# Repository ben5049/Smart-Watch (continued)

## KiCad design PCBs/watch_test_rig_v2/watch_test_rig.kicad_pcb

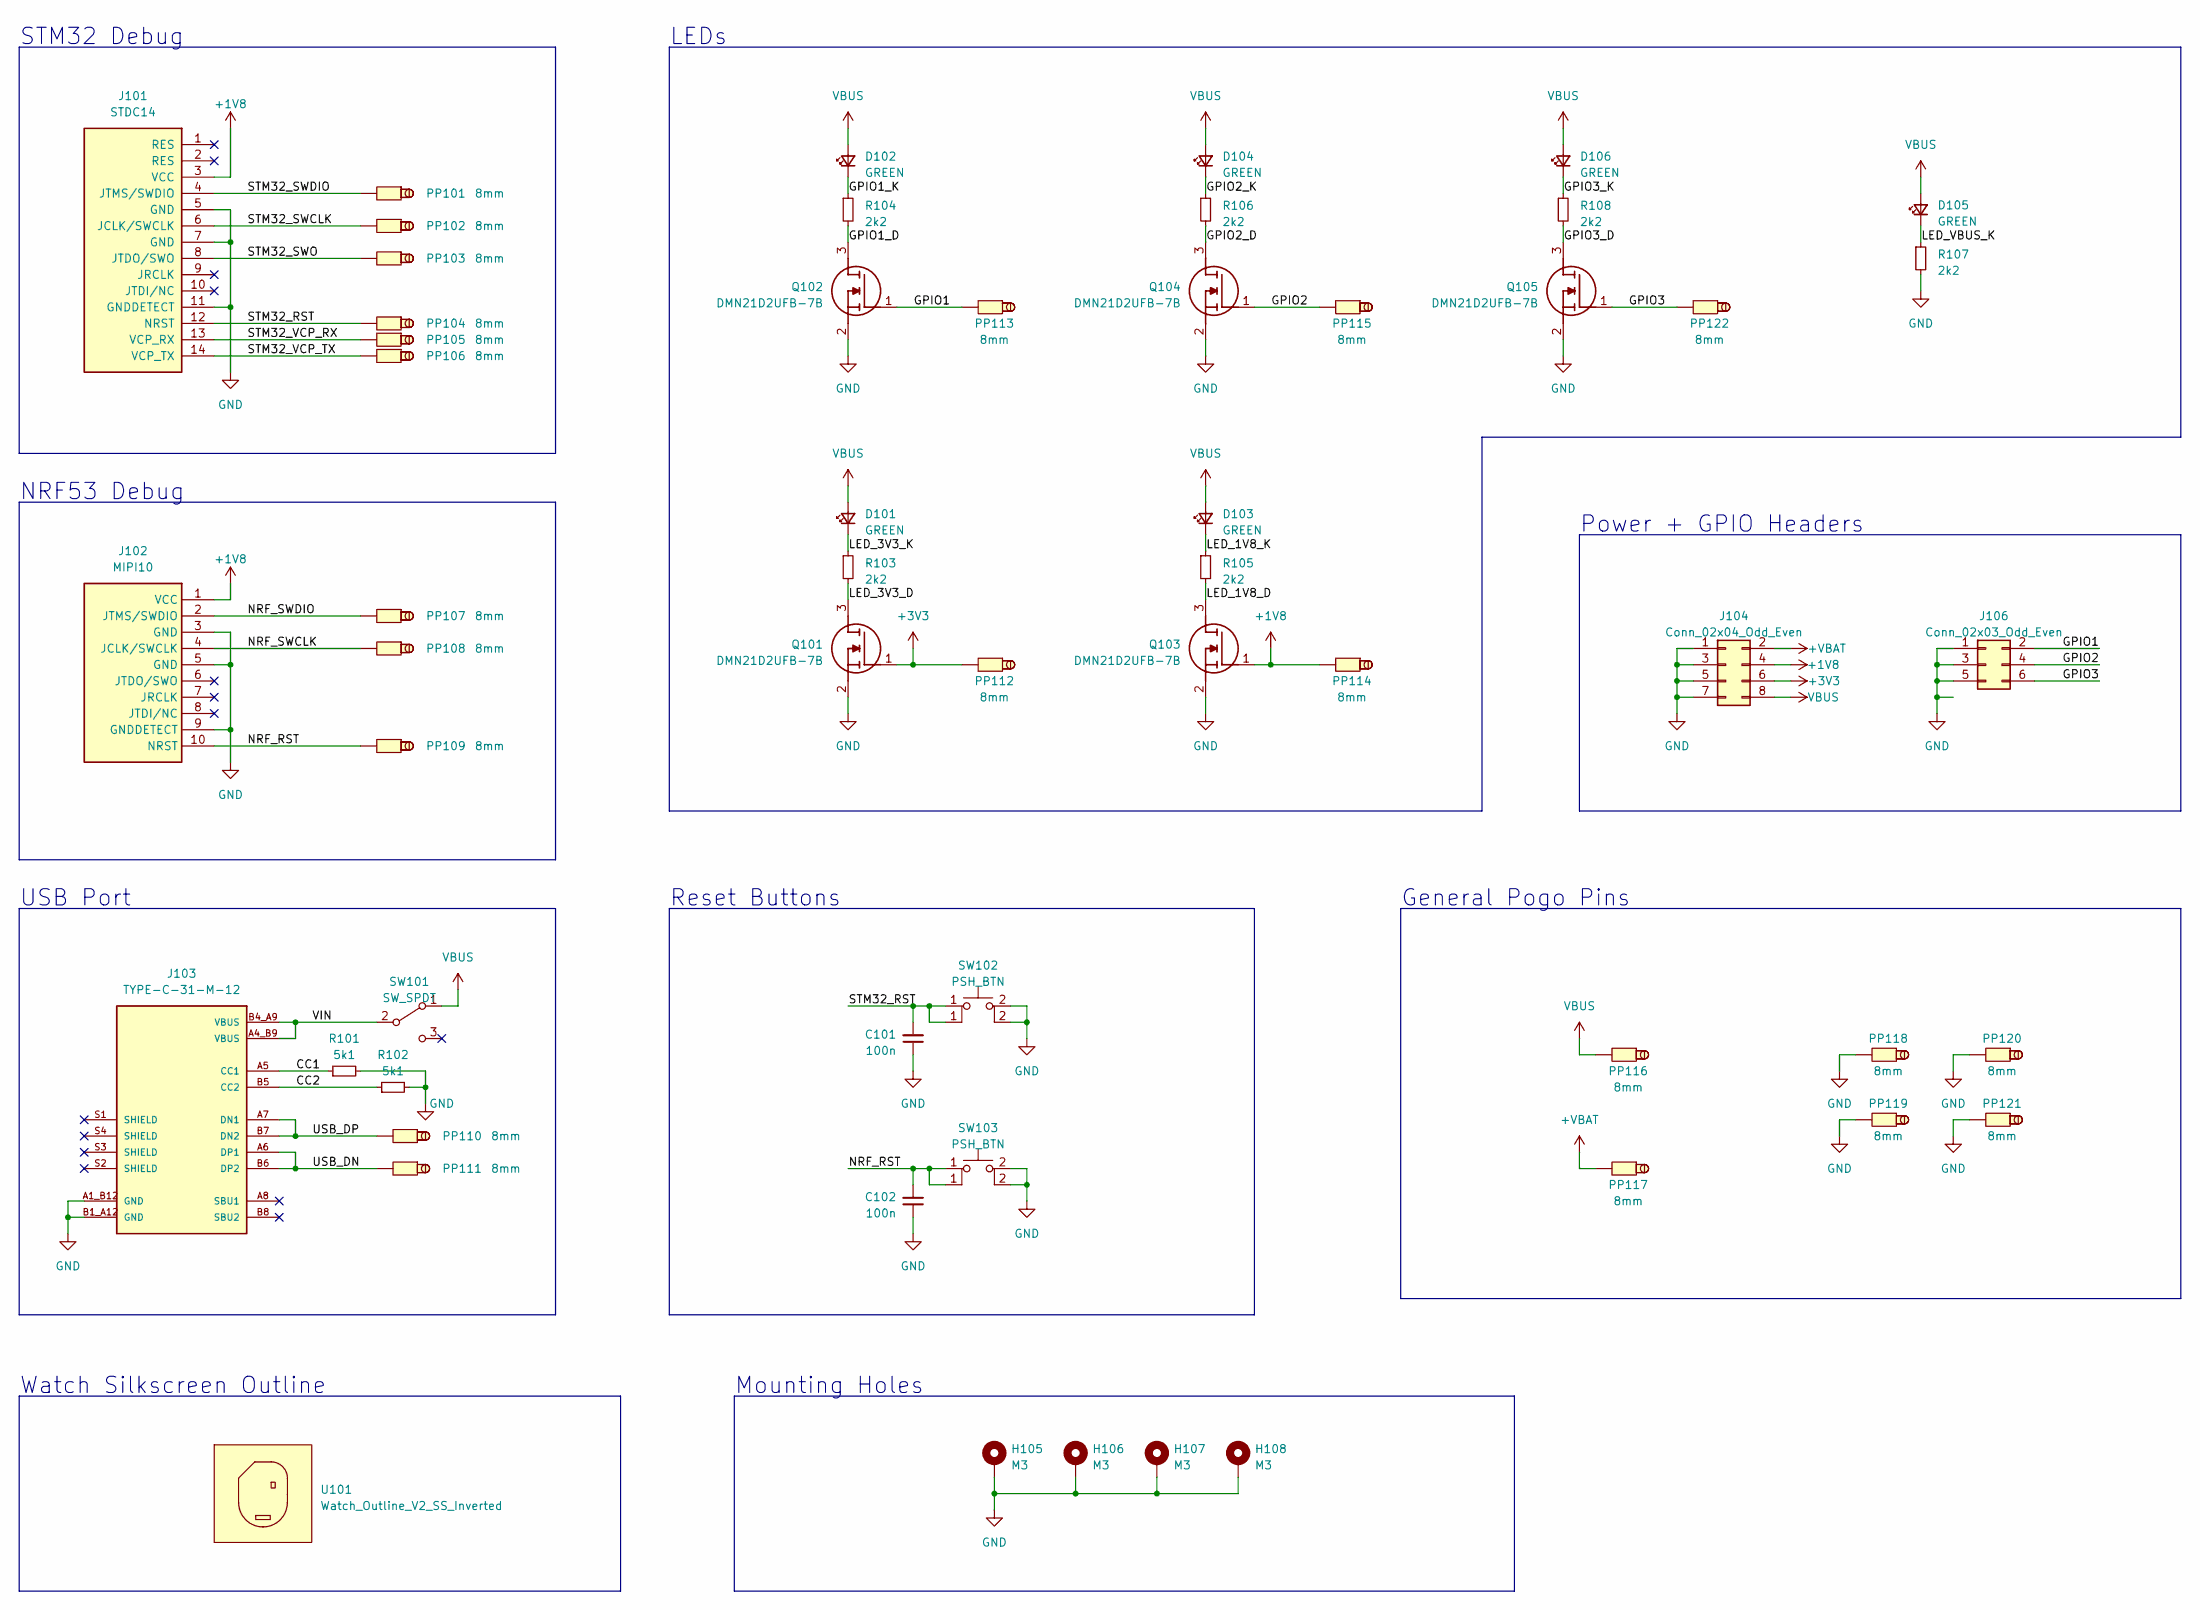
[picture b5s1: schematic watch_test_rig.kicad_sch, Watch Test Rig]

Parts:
C101, C102: 100n; C_0402_1005Metric
D101, D102, D103, D104, D105, D106: GREEN; D_0603_1608Metric
H105, H106, H107, H108: M3; MountingHole_3.2mm_M3_DIN965_Pad_TopBottom
J101: STDC14
J102: MIPI10
J103: TYPE-C-31-M-12; PARTREV 2020.12.08
J104: Conn_02x04_Odd_Even; PinHeader_2x04_P2.54mm_Vertical
J106: Conn_02x03_Odd_Even; PinHeader_2x03_P2.54mm_Vertical
PP101, PP102, PP103, PP104, PP105, PP106, PP107, PP108, PP109, PP110, PP111, PP112, PP113, PP114, PP115, PP116, PP117, PP118, PP119, PP120, PP121, PP122: 8mm; Pogo_Pin_8mm_SMD
Q101, Q102, Q103, Q104, Q105: DMN21D2UFB-7B; DMN21D2UFB7B; Mouser Part Number 621-DMN21D2UFB-7B
R101, R102: 5k1; R_0402_1005Metric
R103, R104, R105, R106, R107, R108: 2k2; R_0402_1005Metric
SW101: SW_SPDT; PinHeader_1x03_P2.54mm_Vertical
SW102, SW103: PSH_BTN; SW_PUSH_6mm_H5mm
U101: Watch_Outline_V2_SS_Inverted; Watch Outline V2 SS Inverted

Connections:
+1V8: J101.3 (VCC), J102.1 (VCC), J104.4, PP114.1, Q103.1 (G)
+3V3: J104.6, PP112.1, Q101.1 (G)
+VBAT: J104.2, PP117.1
/CC1: J103.A5 (CC1), R101.1
/CC2: J103.B5 (CC2), R102.1
/GPIO1: J106.2, PP113.1, Q102.1 (G)
/GPIO1_D: Q102.3 (D), R104.2
/GPIO1_K: D102.1 (K), R104.1
/GPIO2: J106.4, PP115.1, Q104.1 (G)
/GPIO2_D: Q104.3 (D), R106.2
/GPIO2_K: D104.1 (K), R106.1
/GPIO3: J106.6, PP122.1, Q105.1 (G)
/GPIO3_D: Q105.3 (D), R108.2
/GPIO3_K: D106.1 (K), R108.1
/LED_1V8_D: Q103.3 (D), R105.2
/LED_1V8_K: D103.1 (K), R105.1
/LED_3V3_D: Q101.3 (D), R103.2
/LED_3V3_K: D101.1 (K), R103.1
/LED_VBUS_K: D105.1 (K), R107.1
/NRF_RST: C102.2, J102.10 (NRST), PP109.1, SW103.1
/NRF_SWCLK: J102.4 (JCLK/SWCLK), PP108.1
/NRF_SWDIO: J102.2 (JTMS/SWDIO), PP107.1
/STM32_RST: C101.2, J101.12 (NRST), PP104.1, SW102.1
/STM32_SWCLK: J101.6 (JCLK/SWCLK), PP102.1
/STM32_SWDIO: J101.4 (JTMS/SWDIO), PP101.1
/STM32_SWO: J101.8 (JTDO/SWO), PP103.1
/STM32_VCP_RX: J101.13 (VCP_RX), PP105.1
/STM32_VCP_TX: J101.14 (VCP_TX), PP106.1
/USB_DN: J103.A6 (DP1), J103.B6 (DP2), PP111.1
/USB_DP: J103.A7 (DN1), J103.B7 (DN2), PP110.1
/VIN: J103.A4_B9 (VBUS), J103.B4_A9 (VBUS), SW101.2 (B)
GND: C101.1, C102.1, H105.1, H106.1, H107.1, H108.1, J101.5 (GND), J101.7 (GND), J101.11 (GNDDETECT), J102.3 (GND), J102.5 (GND), J102.9 (GNDDETECT), J103.A1_B12 (GND), J103.B1_A12 (GND), J104.1, J104.3, J104.5, J104.7, J106.1, J106.3, J106.5, PP118.1, PP119.1, PP120.1, PP121.1, Q101.2 (S), Q102.2 (S), Q103.2 (S), Q104.2 (S), Q105.2 (S), R101.2, R102.2, R107.2, SW102.2, SW103.2
VBUS: D101.2 (A), D102.2 (A), D103.2 (A), D104.2 (A), D105.2 (A), D106.2 (A), J104.8, PP116.1, SW101.1 (A)

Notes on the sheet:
Mounting Holes
Watch Silkscreen Outline
STM32 Debug
USB Port
Reset Buttons
General Pogo Pins
Power + GPIO Headers
LEDs
NRF53 Debug

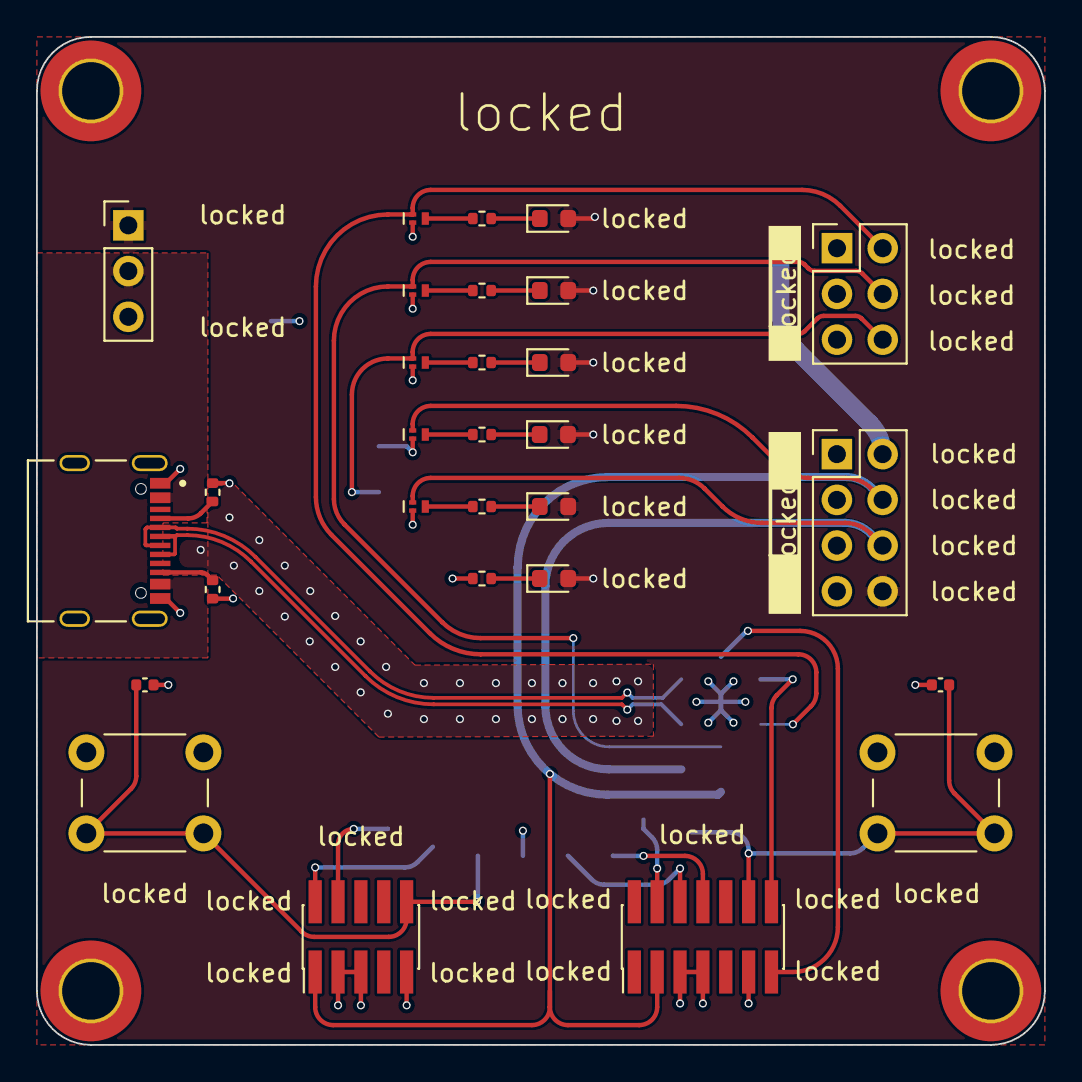
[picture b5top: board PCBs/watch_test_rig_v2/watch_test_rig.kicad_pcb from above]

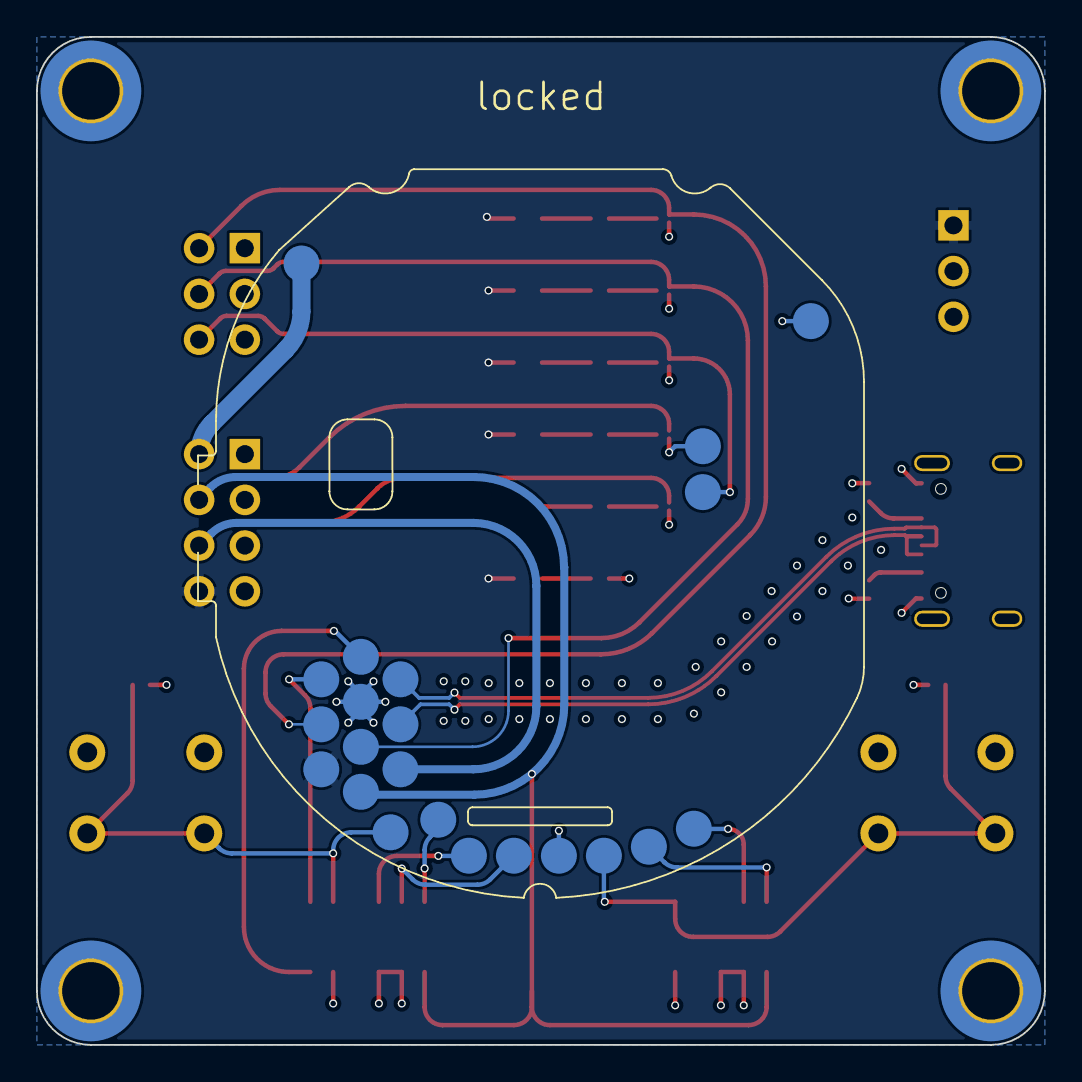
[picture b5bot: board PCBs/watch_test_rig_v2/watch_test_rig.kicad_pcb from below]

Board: 4 copper layers, 56.0 x 56.0 mm, 56 parts (22 on the bottom side), 33 nets.

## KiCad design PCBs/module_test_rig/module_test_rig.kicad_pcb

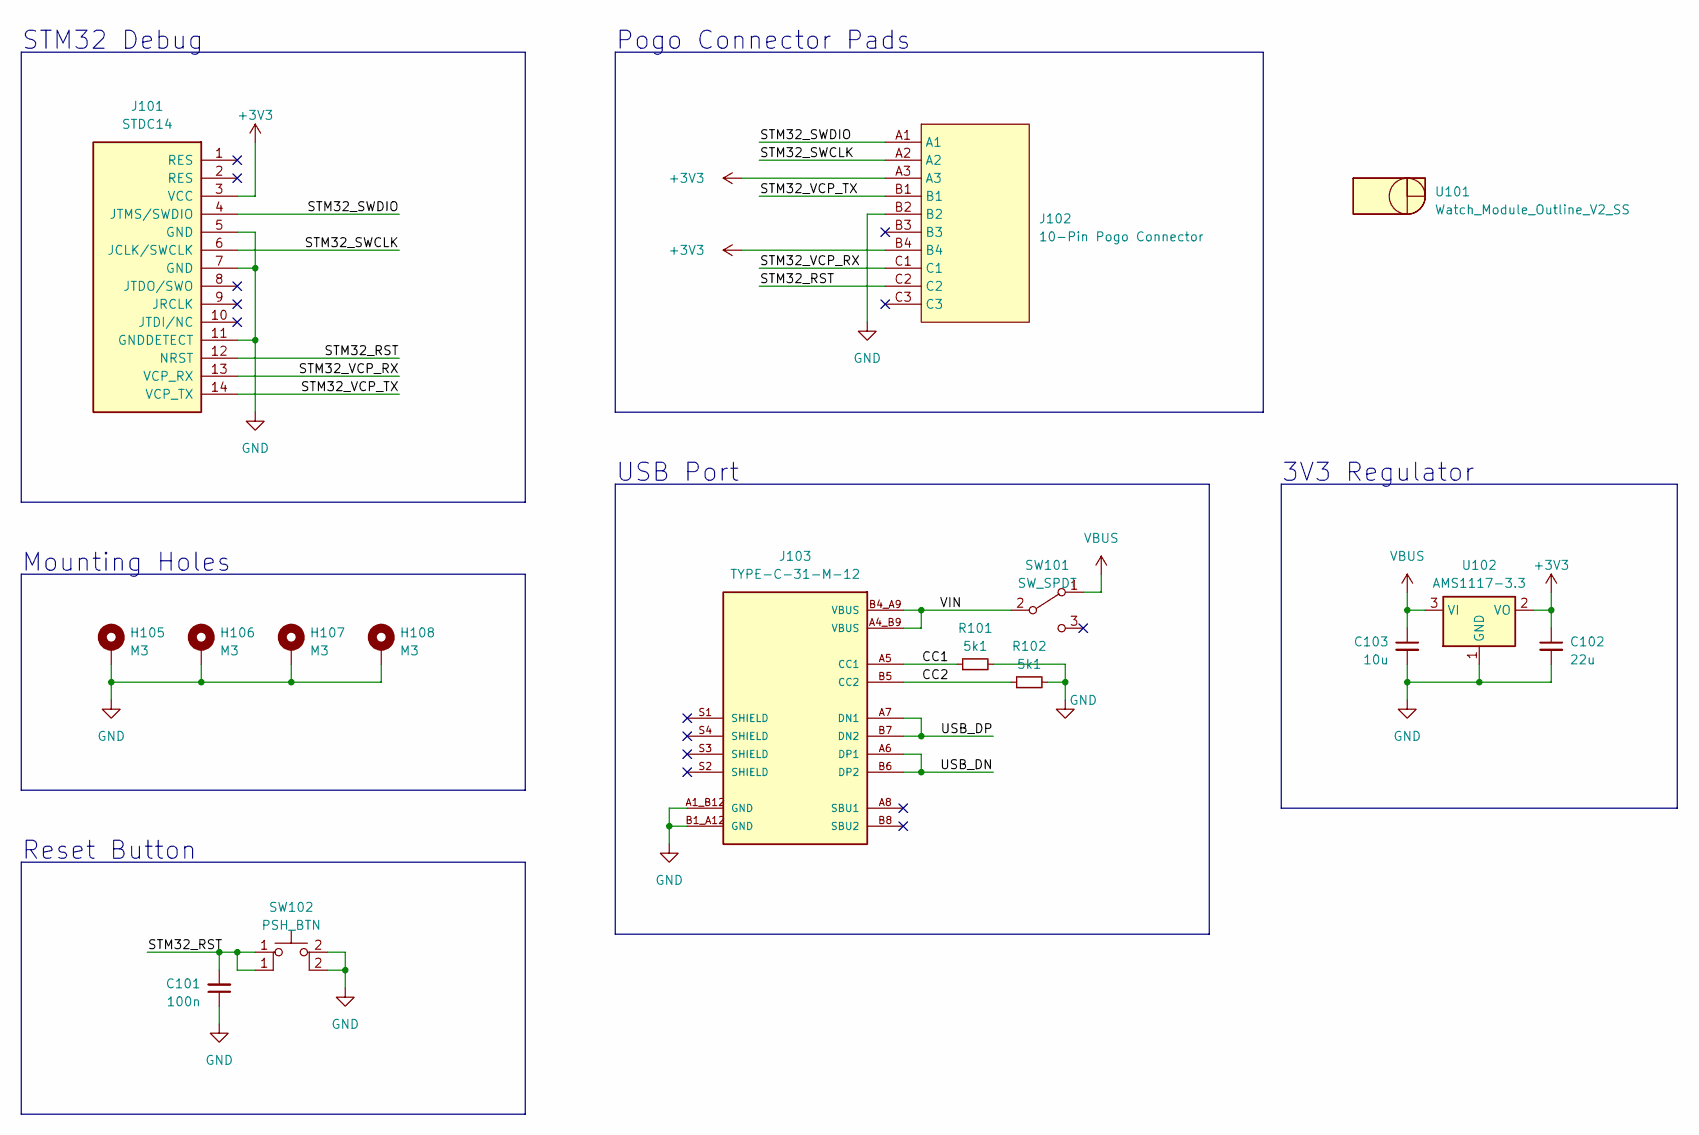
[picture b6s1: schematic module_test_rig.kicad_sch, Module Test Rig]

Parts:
C101: 100n; C_0402_1005Metric
C102: 22u; C_0402_1005Metric
C103: 10u; C_0402_1005Metric
H105, H106, H107, H108: M3; MountingHole_3.2mm_M3_DIN965_Pad_TopBottom
J101: STDC14
J102: 10-Pin Pogo Connector
J103: TYPE-C-31-M-12; PARTREV 2020.12.08
R101, R102: 5k1; R_0402_1005Metric
SW101: SW_SPDT; PinHeader_1x03_P2.54mm_Vertical
SW102: PSH_BTN; SW_PUSH_6mm_H5mm
U101: Watch_Module_Outline_V2_SS; Watch Module Outline V2 SS
U102: AMS1117-3.3; SOT-223-3_TabPin2

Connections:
+3V3: C102.1, J101.3 (VCC), J102.A3, J102.B4, U102.2 (VO)
/CC1: J103.A5 (CC1), R101.1
/CC2: J103.B5 (CC2), R102.1
/STM32_RST: C101.2, J101.12 (NRST), J102.C2, SW102.1
/STM32_SWCLK: J101.6 (JCLK/SWCLK), J102.A2
/STM32_SWDIO: J101.4 (JTMS/SWDIO), J102.A1
/STM32_VCP_RX: J101.13 (VCP_RX), J102.C1
/STM32_VCP_TX: J101.14 (VCP_TX), J102.B1
/USB_DN: J103.A6 (DP1), J103.B6 (DP2)
/USB_DP: J103.A7 (DN1), J103.B7 (DN2)
/VIN: J103.A4_B9 (VBUS), J103.B4_A9 (VBUS), SW101.2 (B)
GND: C101.1, C102.2, C103.2, H105.1, H106.1, H107.1, H108.1, J101.5 (GND), J101.7 (GND), J101.11 (GNDDETECT), J102.B2, J103.A1_B12 (GND), J103.B1_A12 (GND), R101.2, R102.2, SW102.2, U102.1 (GND)
VBUS: C103.1, SW101.1 (A), U102.3 (VI)

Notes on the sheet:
Mounting Holes
STM32 Debug
USB Port
Reset Button
Pogo Connector Pads
3V3 Regulator

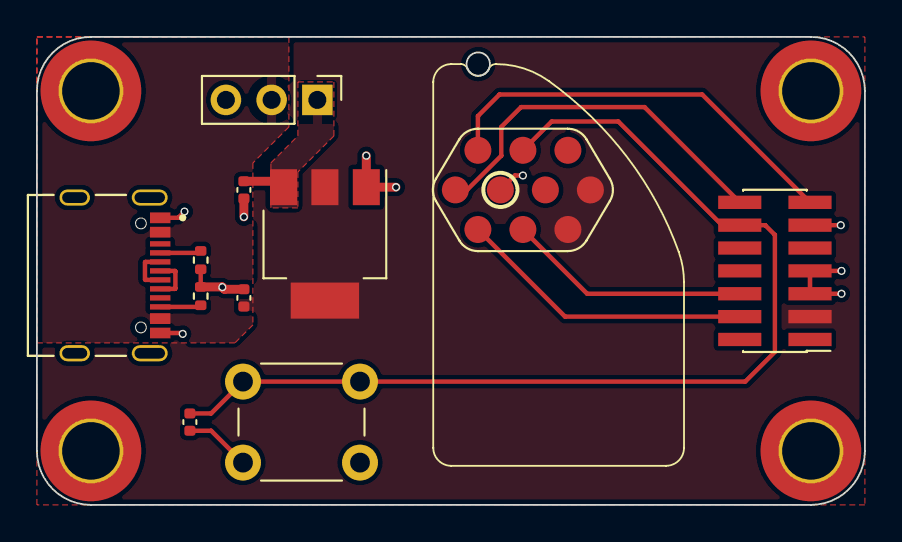
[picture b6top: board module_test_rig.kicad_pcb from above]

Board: 2 copper layers, 46.0 x 26.0 mm, 16 parts (0 on the bottom side), 13 nets.

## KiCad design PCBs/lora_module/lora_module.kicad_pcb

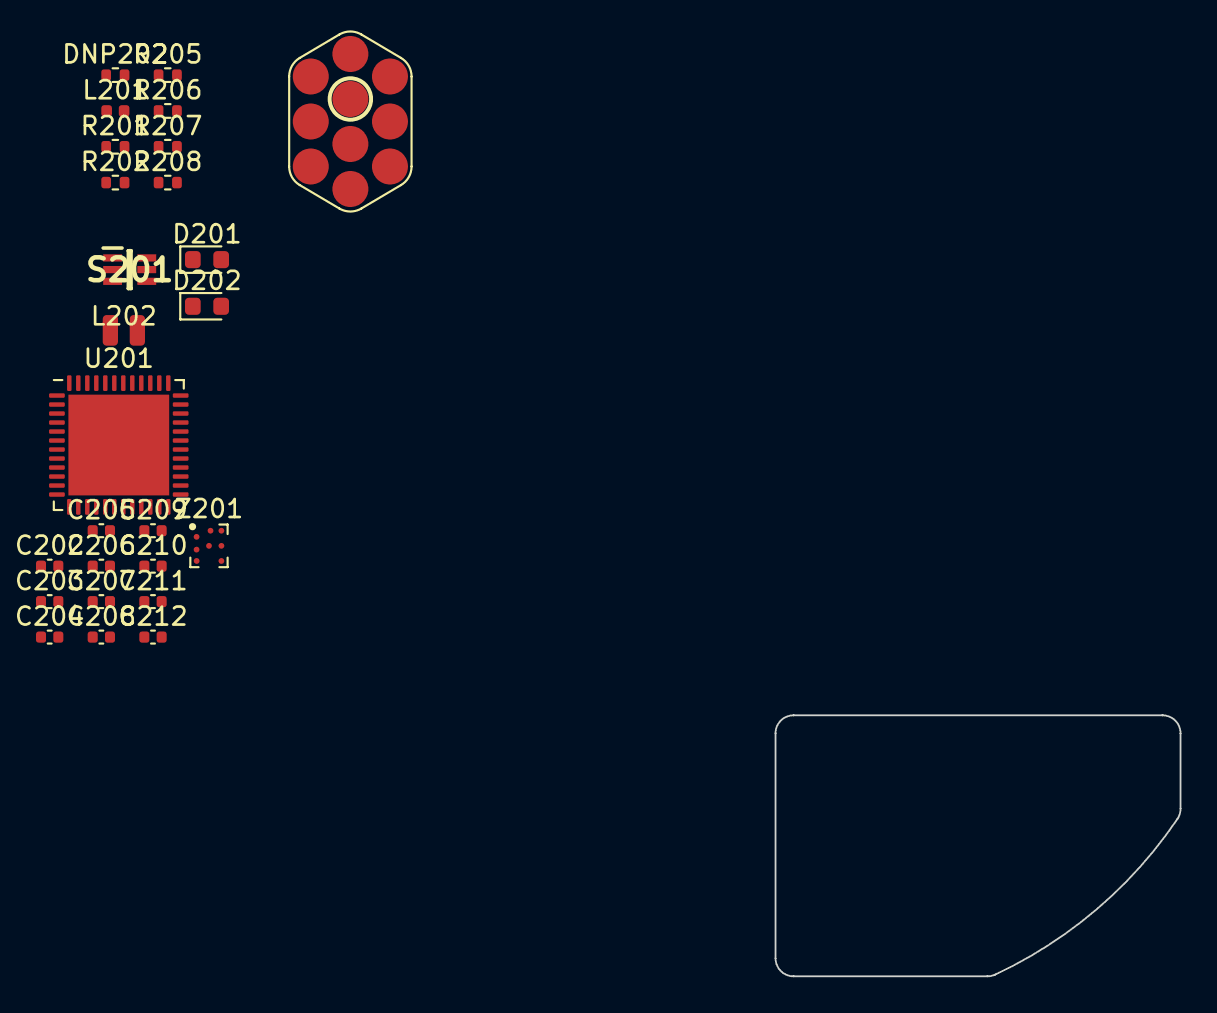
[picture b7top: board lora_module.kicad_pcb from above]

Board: 2 copper layers, 22.5 x 14.5 mm, 27 parts (0 on the bottom side), 13 nets, no tracks yet.

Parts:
C202, C203, C206, C210: 100n; C_0402_1005Metric
C204: 68p; C_0402_1005Metric
C205: 470n; C_0402_1005Metric
C207, C212: 4u7; C_0402_1005Metric
C208: 10n; C_0402_1005Metric
C209, C211: 1u; C_0402_1005Metric
D201: LEDR; LED_0603_1608Metric
D202: LEDB; LED_0603_1608Metric
DNP202: 10k; R_0402_1005Metric
J401: 10-Pin_Pogo_Connector_Male; 10-Pin Pogo Connector Male
L201: 47n; L_0402_1005Metric
L202: 15u; Inductor 0806 (2016)
R201, R202: 1k; R_0402_1005Metric
R205, R207, R208: 10k; R_0402_1005Metric
R206: 0R; R_0402_1005Metric
S201: PE42421SCAA-Z; SOT65P210X110-6N
U101: Watch_Module_Outline_V1; Watch Module Outline V1
U201: STM32WL55CCUx; QFN-48-1EP_7x7mm_P0.5mm_EP5.6x5.6mm
Z201: BALFHB-WL-02D3

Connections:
+3V3: C203.1, C206.1, C207.1, C208.1, C209.1, C210.1, C211.1, C212.1, DNP202.1, J401.A3, R207.2, R208.2
/STM32WL55/CTRL1: R208.1, S201.6 (VDD)
/STM32WL55/CTRL2: R207.1, S201.4 (CTRL)
/STM32WL55/LoRa_BOOT: DNP202.2, R205.1
/STM32WL55/LoRa_LEDB_C: D202.1 (K), R202.1
/STM32WL55/LoRa_LEDR_C: D201.1 (K), R201.1
/STM32WL55/RFI: S201.3 (RF2), Z201.C3 (RFI_IN)
/STM32WL55/RFO: S201.1 (RF1), Z201.C1 (RFO_OUT)
/STM32WL55/RFO_HP1: L201.2, R206.1
/STM32WL55/RFO_HP2: R206.2, Z201.A1 (RFO_IN)
/STM32WL55/VDDRF1V5: C205.1, L202.1
/STM32WL55/VR_PA: C202.1, C204.1, L201.1
GND: C202.2, C203.2, C204.2, C205.2, C206.2, C207.2, C208.2, C209.2, C210.2, C211.2, C212.2, J401.B2, R201.2, R202.2, R205.2, S201.2 (GND), Z201.B1 (GND), Z201.B2 (GND), Z201.C2 (GND)

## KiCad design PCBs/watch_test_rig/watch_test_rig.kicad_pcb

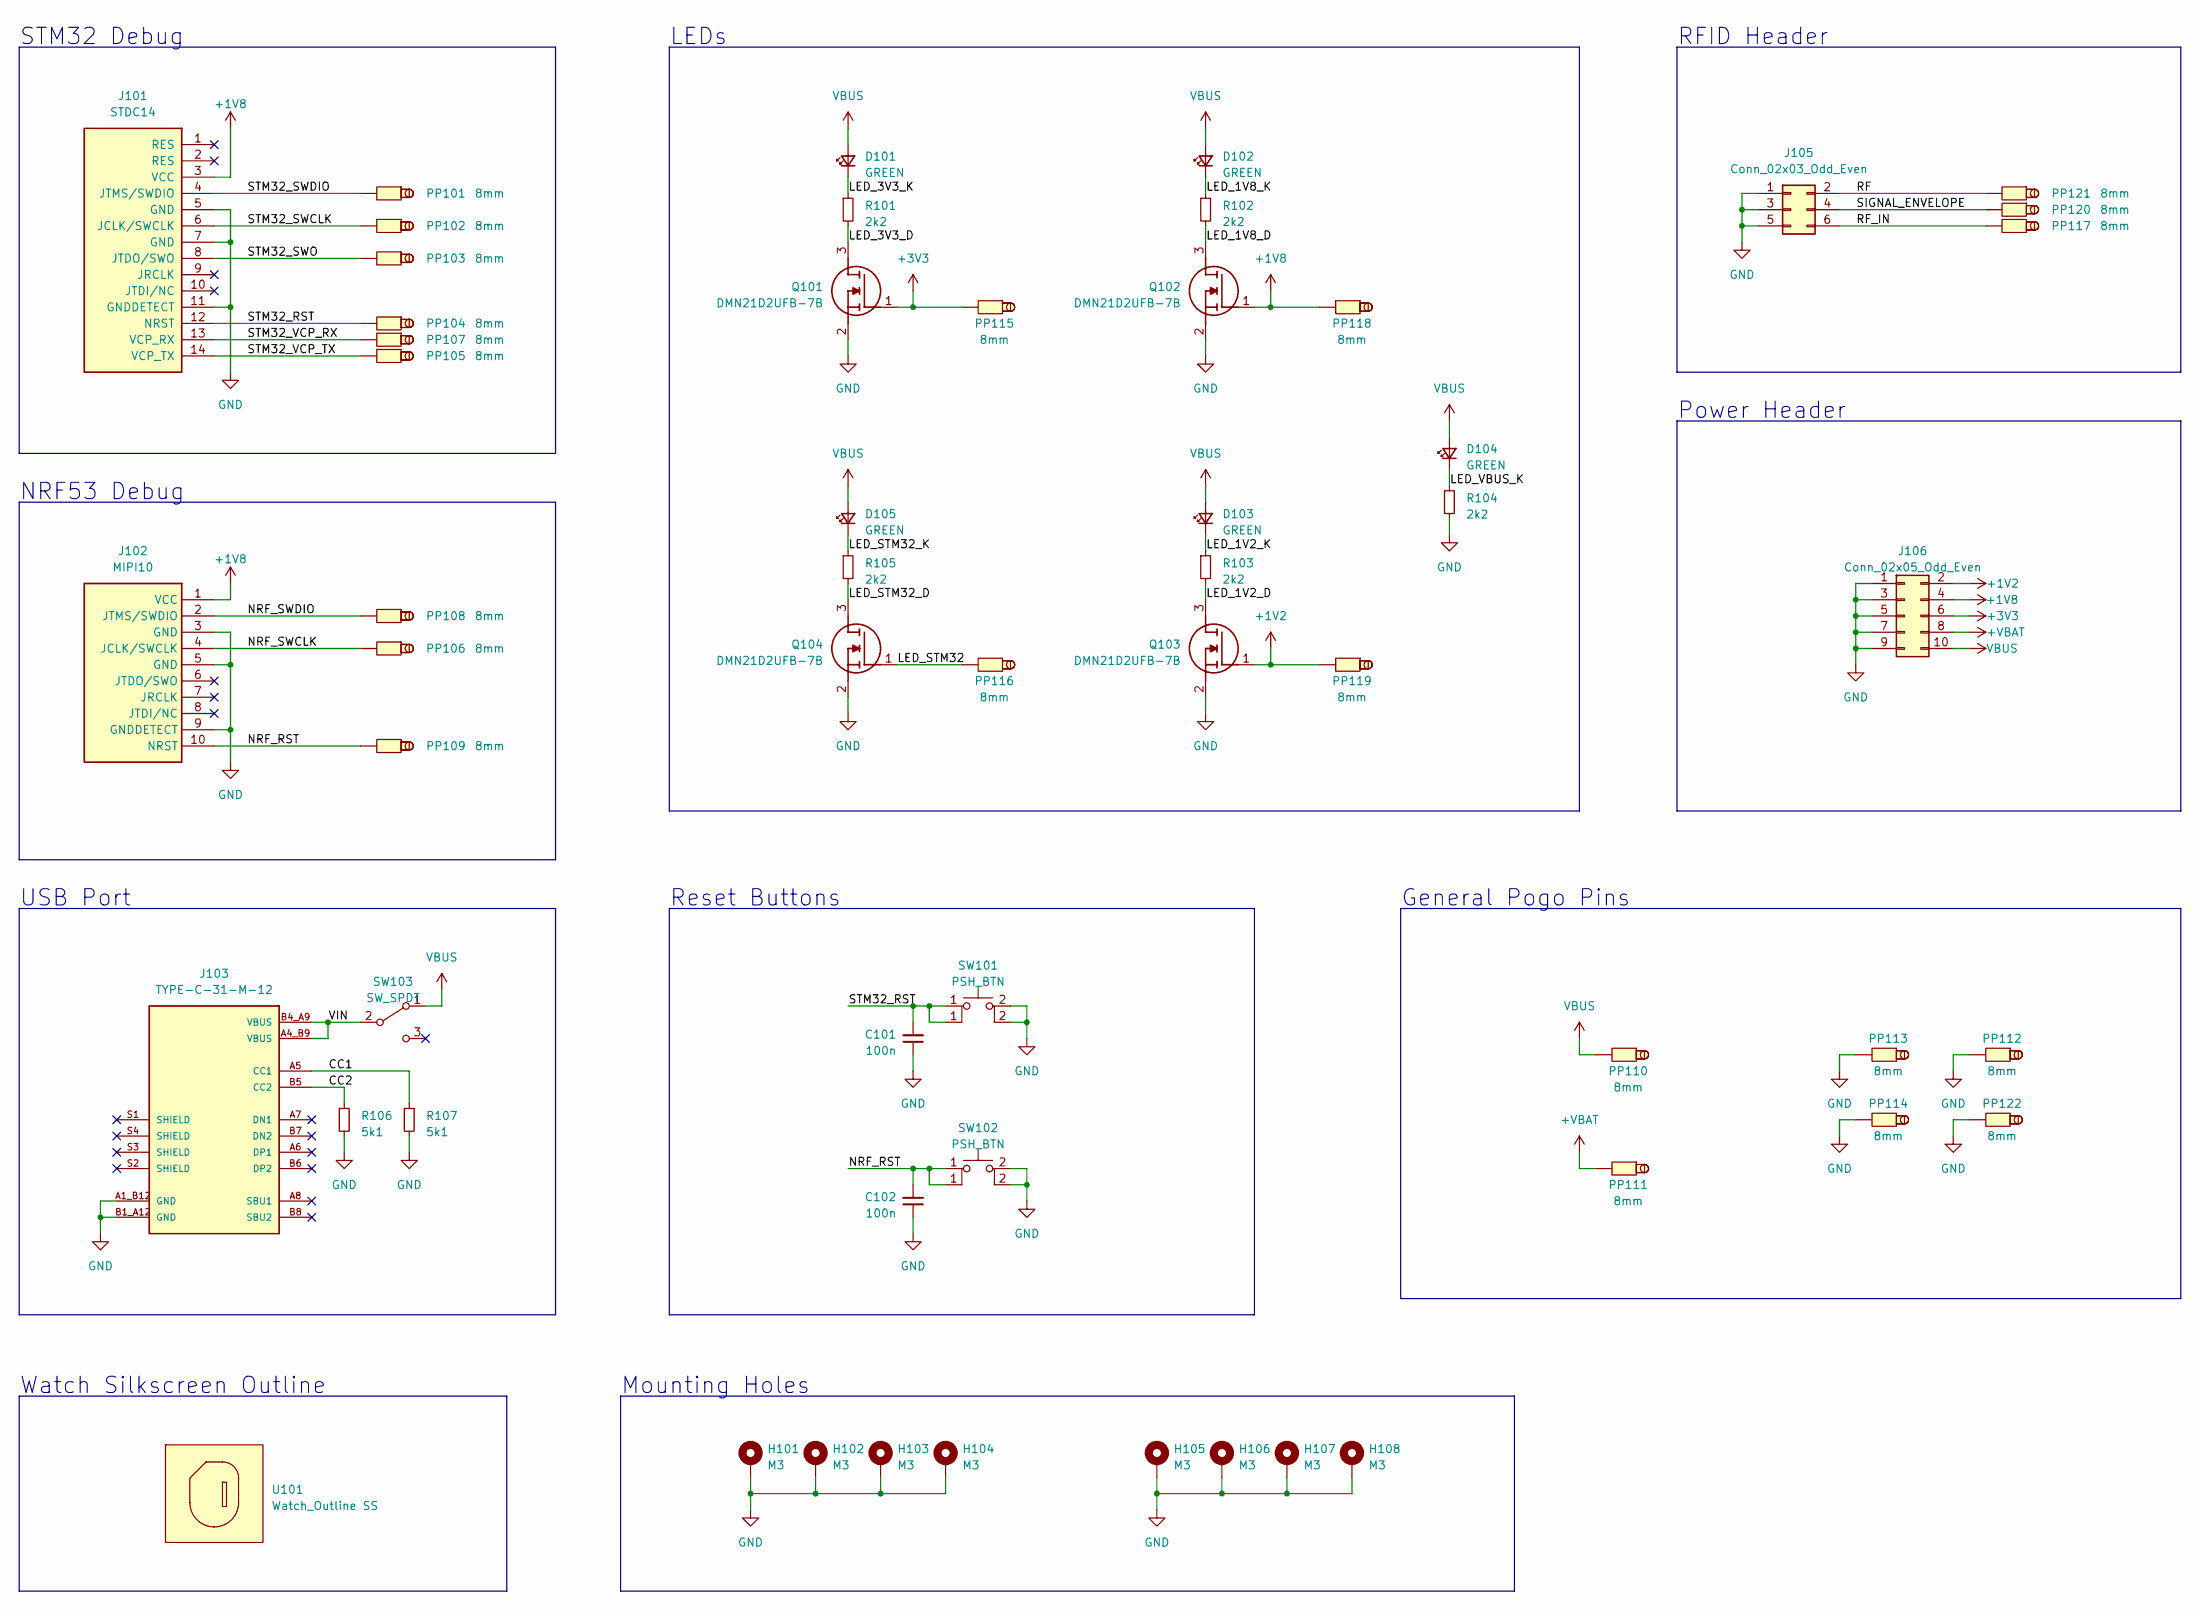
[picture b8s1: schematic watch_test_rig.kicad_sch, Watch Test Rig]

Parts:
C101, C102: 100n; C_0402_1005Metric
D101, D102, D103, D104, D105: GREEN; D_0603_1608Metric
H101, H102, H103, H104, H105, H106, H107, H108: M3; MountingHole_3.2mm_M3_DIN965_Pad_TopBottom
J101: STDC14
J102: MIPI10
J103: TYPE-C-31-M-12; PARTREV 2020.12.08
J105: Conn_02x03_Odd_Even; PinHeader_2x03_P2.54mm_Vertical
J106: Conn_02x05_Odd_Even; PinHeader_2x05_P2.54mm_Vertical
PP101, PP102, PP103, PP104, PP105, PP106, PP107, PP108, PP109, PP110, PP111, PP112, PP113, PP114, PP115, PP116, PP117, PP118, PP119, PP120, PP121, PP122: 8mm; Pogo_Pin_8mm
Q101, Q102, Q103, Q104: DMN21D2UFB-7B; DMN21D2UFB7B; Mouser Part Number 621-DMN21D2UFB-7B
R101, R102, R103, R104, R105: 2k2; R_0402_1005Metric
R106, R107: 5k1; R_0402_1005Metric
SW101, SW102: PSH_BTN; SW_PUSH_6mm_H5mm
SW103: SW_SPDT; PinHeader_1x03_P2.54mm_Vertical
U101: Watch_Outline SS; Watch Outline V1 SS

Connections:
+1V2: J106.2, PP119.1, Q103.1 (G)
+1V8: J101.3 (VCC), J102.1 (VCC), J106.4, PP118.1, Q102.1 (G)
+3V3: J106.6, PP115.1, Q101.1 (G)
+VBAT: J106.8, PP111.1
/CC1: J103.A5 (CC1), R107.1
/CC2: J103.B5 (CC2), R106.1
/LED_1V2_D: Q103.3 (D), R103.2
/LED_1V2_K: D103.1 (K), R103.1
/LED_1V8_D: Q102.3 (D), R102.2
/LED_1V8_K: D102.1 (K), R102.1
/LED_3V3_D: Q101.3 (D), R101.2
/LED_3V3_K: D101.1 (K), R101.1
/LED_STM32: PP116.1, Q104.1 (G)
/LED_STM32_D: Q104.3 (D), R105.2
/LED_STM32_K: D105.1 (K), R105.1
/LED_VBUS_K: D104.1 (K), R104.1
/NRF_RST: C102.2, J102.10 (NRST), PP109.1, SW102.1
/NRF_SWCLK: J102.4 (JCLK/SWCLK), PP106.1
/NRF_SWDIO: J102.2 (JTMS/SWDIO), PP108.1
/RF: J105.2, PP121.1
/RF_IN: J105.6, PP117.1
/SIGNAL_ENVELOPE: J105.4, PP120.1
/STM32_RST: C101.2, J101.12 (NRST), PP104.1, SW101.1
/STM32_SWCLK: J101.6 (JCLK/SWCLK), PP102.1
/STM32_SWDIO: J101.4 (JTMS/SWDIO), PP101.1
/STM32_SWO: J101.8 (JTDO/SWO), PP103.1
/STM32_VCP_RX: J101.13 (VCP_RX), PP107.1
/STM32_VCP_TX: J101.14 (VCP_TX), PP105.1
/VIN: J103.A4_B9 (VBUS), J103.B4_A9 (VBUS), SW103.2 (B)
GND: C101.1, C102.1, H101.1, H102.1, H103.1, H104.1, H105.1, H106.1, H107.1, H108.1, J101.5 (GND), J101.7 (GND), J101.11 (GNDDETECT), J102.3 (GND), J102.5 (GND), J102.9 (GNDDETECT), J103.A1_B12 (GND), J103.B1_A12 (GND), J105.1, J105.3, J105.5, J106.1, J106.3, J106.5, J106.7, J106.9, PP112.1, PP113.1, PP114.1, PP122.1, Q101.2 (S), Q102.2 (S), Q103.2 (S), Q104.2 (S), R104.2, R106.2, R107.2, SW101.2, SW102.2
VBUS: D101.2 (A), D102.2 (A), D103.2 (A), D104.2 (A), D105.2 (A), J106.10, PP110.1, SW103.1 (A)

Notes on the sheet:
Mounting Holes
Watch Silkscreen Outline
STM32 Debug
USB Port
RFID Header
Reset Buttons
General Pogo Pins
Power Header
LEDs
NRF53 Debug

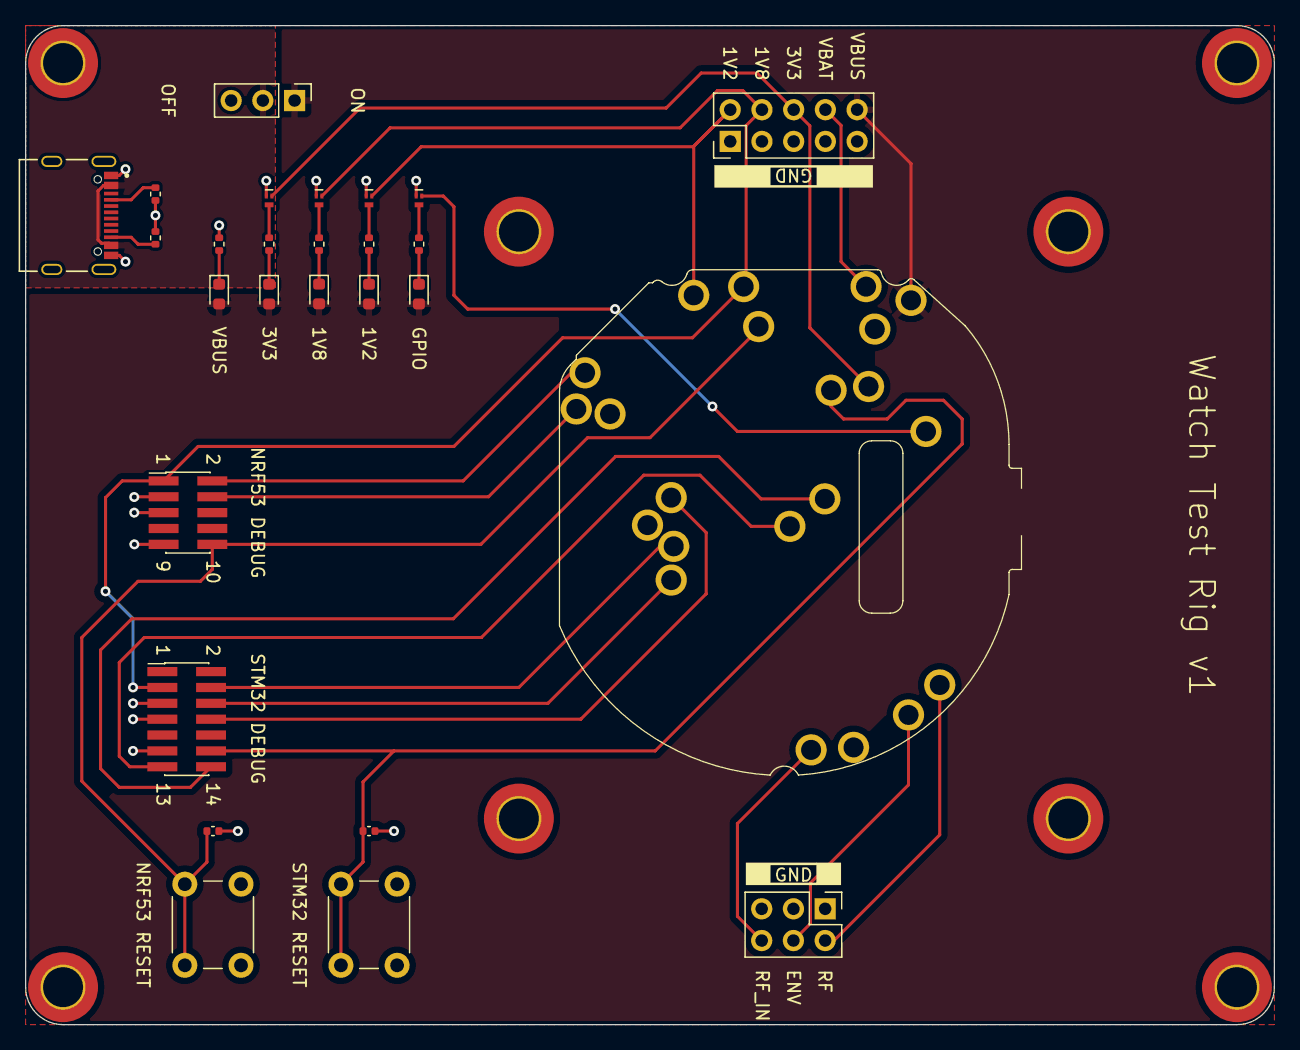
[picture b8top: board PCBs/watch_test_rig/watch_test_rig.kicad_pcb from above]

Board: 2 copper layers, 100.0 x 80.0 mm, 57 parts (0 on the bottom side), 31 nets.

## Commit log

2023-12-12 Started main PCB development
2023-12-13 More PCB progress
2023-12-13 Created "Component Selection.md", minor PCB schematic updates
2023-12-15 Created board outline
2023-12-15 All components symbols, footprints and models paths are relative to project for better portability.
2023-12-17 Created firmware project
2023-12-17 Schematic and pcb progress
2023-12-18 PCB Schematic progress
2023-12-18 Added connector symbols and footprints
2023-12-19 Main PCB schematic almost complete
2023-12-20 Progress with schematic and RFID simulations
2023-12-21 Schematic finished and BOM started
2023-12-21 Created test rig schematic
2023-12-22 Started routing main PCB
2023-12-23 Main PCB placement and routing progress
2023-12-23 287 Connections unrouted
2023-12-23 224 Unrouted traces
2023-12-24 69 Unrouted traces
2023-12-24 33 Unrouted traces
2023-12-24 Main PCB finished
2023-12-25 Test rig board finished
2023-12-25 Created schematic PDFs
2023-12-27 New display, started PCB revision 2
2023-12-27 Schematic v2 complete
2023-12-27 ignore
2023-12-27 252 Unrouted traces
2023-12-28 262 Unrouted traces, fixed clearance issues
2023-12-29 190 Unrouted traces
2023-12-30 Main board v2 complete
2023-12-30 Added useful links
2023-12-30 Added EEPROM
2023-12-31 Main board and test rig complete & ordered.
2024-01-01 Added watch_test_rig_support
2024-01-02 RFID Module progress
2024-01-03 RFID PCB Done, started lower flex PCB
2024-01-04 Flex PCB finished. Need to rotate RFID transponder coil.
2024-01-05 3D Modelling complete, need to rework some PCBs
2024-01-05 RFID Module v1.1 complete
2024-01-06 RFID Module v1.1 complete (+default firmware)
2024-01-07 Added comments to RFID module and created gerber files.
2024-01-07 Watch main BOM progress.
2024-01-08 Flex PCB and RFID PCB ordered.
2024-01-08 All BOMs complete
2024-01-09 Component purchasing complete
2024-01-09 Fixed flex PCB via in pad issue.
2024-01-09 Default firmware finished, minor main PCB update
2024-01-10 Minor PCB fixes
2024-01-10 Added CAD folder and test rig frame models
2024-01-11 Created ADP5360 library
2024-01-12 GFXMMU Configuration updated
2024-01-12 Created display_pixel_config.xlsx
2024-01-13 Fixed coordinate generation program
2024-01-14 Bottom frame finished
2024-01-15 Cleaning files
2024-01-16 Refreshed IBOM for main PCB & test rig
2024-01-17 Added "Future Changes.md"
2024-01-17 Added blink program
2024-01-17 ADP5360 driver working
2024-01-17 Changed firmware file structure & added functionality to enter shipment mode via MR pin on the ADP5360
2024-01-18 Created watch main board V3 Kicad project
2024-01-19 EEPROM Driver working
2024-01-20 DRV2605 Driver progress
2024-01-20 Created "EEPROM.h" and "EEPROM.c" to standardise EEPROM interfaces
2024-01-22 Updated default_configuration_v3
2024-01-22 Tidying, improved documentation, and created MAX30102 driver template
2024-01-23 Updated READMEs
2024-01-25 Started watch_main_v3
2024-01-25 watch_main_v3 updates
2024-01-26 watch_main_v3 updated layout
2024-01-26 watch_main_v3 removed unnecessary capacitors from schematic.
2024-01-27 watch_main_v3 WiFi/Bluetooth schematic done
2024-01-31 Created touch connector footprint
2024-02-01 Swapped in new touch connector footprint
2024-02-02 Updated .gitignore
2024-02-03 Created "display_demo" project, currently not working
2024-03-26 PCB V3 progress
2024-03-28 Hard routing done
2024-03-30 Main board version 3.0 done and purchased
2024-03-30 Upadated documentation
2024-04-02 Small PCB tweaks
2024-04-05 Minor changes
2024-05-06 Updated gitignore
2024-05-06 Updated gitignore again
2024-05-06 DISPLAY WORKS!!!
2024-05-07 Updated column addresses
2024-05-08 TouchGFX works. Need to make DSI HS mode work next.
2024-05-09 Basic GUI works, need to make DSI high speed.
2024-09-27 Backing up changes
2024-10-17 Changed README.md with latest PCB
2025-03-17 Updated gitignore with kicad patterns
2025-03-17 Updated some projects to Kicad 9
